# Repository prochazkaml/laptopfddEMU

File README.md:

# laptopfddEMU
AVR based laptop floppy drive emulator

Consists of 2 MCUs:
- ATmega328PB - runs the actual floppy drive emulator
- ATmega16A - serves as a serial terminal, interfaces to 3x 7-segment displays and 5 buttons

The PCB design with the ATmega328PB (TQFP32) is available in the [kicad](/kicad) directory
(note: the design is bad, the electrolytic cap needs to be as close to the MCU as possible, the current placement causes unexpected issues where the MCU resets randomly - 
just solder another cap directly to the MCU's legs from the programmer/serial side, as you've got nice big pads there).

The "PCB design" with the ATmega16A (DIP40) was improvised and cut out on a piece of raw copper PCB with a knife. No designs available for that, I'm afraid.

Apologies for the lack of documentation on this project, but I was improvising almost everything (as I needed to get this project done extra quick)
and did not keep track of progress very well. Consider building this only if you feel brave enough for it.

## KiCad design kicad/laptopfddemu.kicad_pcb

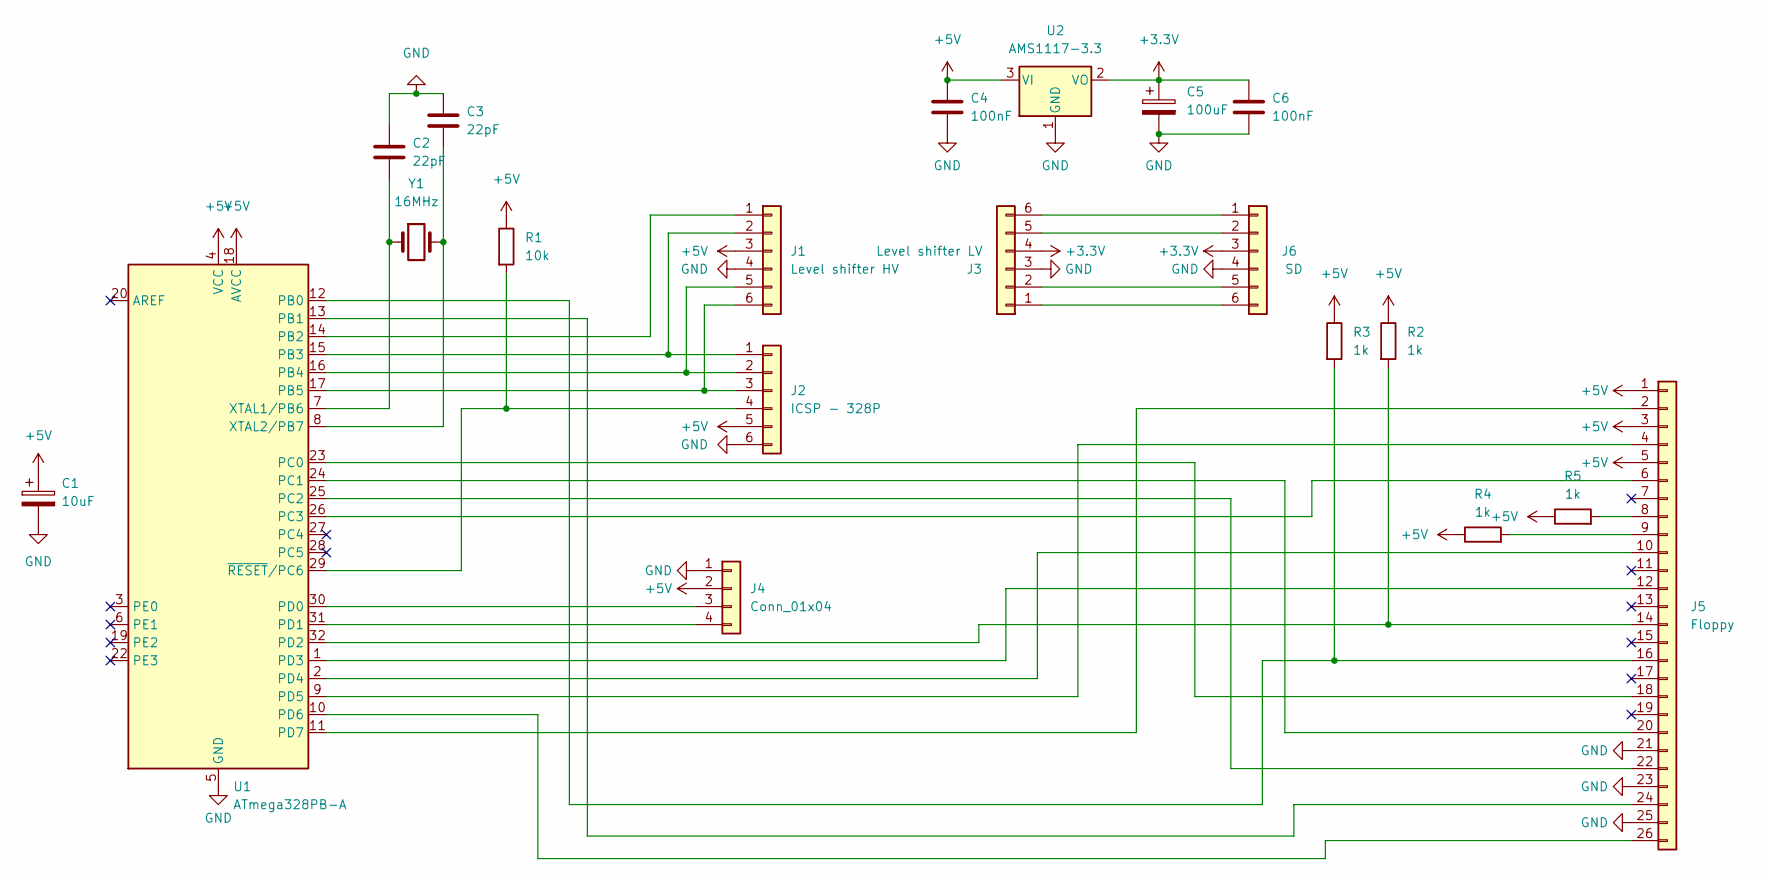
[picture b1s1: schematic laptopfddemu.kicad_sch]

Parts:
C1: 10uF; CP_Radial_D5.0mm_P2.50mm
C2, C3: 22pF; C_Disc_D7.0mm_W2.5mm_P5.00mm
C4, C6: 100nF; C_Disc_D7.0mm_W2.5mm_P5.00mm
C5: 100uF; CP_Radial_D5.0mm_P2.50mm
J1: Level shifter HV; PinHeader_1x06_P2.54mm_Vertical
J2: ICSP - 328P; PinHeader_1x06_P2.54mm_Vertical
J3: Level shifter LV; PinHeader_1x06_P2.54mm_Vertical
J4: Conn_01x04; PinHeader_1x04_P2.54mm_Vertical
J5: Floppy; TE_2-84953-6_1x26-1MP_P1.0mm_Horizontal
J6: SD; PinHeader_1x06_P2.54mm_Vertical
R1: 10k; R_Axial_DIN0207_L6.3mm_D2.5mm_P10.16mm_Horizontal
R2, R3, R4, R5: 1k; R_Axial_DIN0207_L6.3mm_D2.5mm_P10.16mm_Horizontal
U1: ATmega328PB-A; TQFP-32_7x7mm_P0.8mm
U2: AMS1117-3.3; SOT-223-3_TabPin2
Y1: 16MHz; Crystal_HC49-U_Vertical

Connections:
+3.3V: C5.1, C6.1, J3.4, J6.3, U2.2 (VO)
+5V: C1.1, C4.1, J1.3, J2.5, J4.2, J5.1, J5.3, J5.5, R1.1, R2.1, R3.1, R4.1, R5.1, U1.4 (VCC), U1.18 (AVCC), U2.3 (VI)
GND: C1.2, C2.1, C3.1, C4.2, C5.2, C6.2, J1.4, J2.6, J3.3, J4.1, J5.21, J5.23, J5.25, J5.MP, J6.4, U1.5 (GND), U1.21 (GND), U2.1 (GND)
unnamed: C2.2, U1.7 (XTAL1/PB6), Y1.1
unnamed: C3.2, U1.8 (XTAL2/PB7), Y1.2
unnamed: J1.1, U1.14 (PB2)
unnamed: J1.2, J2.1, U1.15 (PB3)
unnamed: J1.5, J2.2, U1.16 (PB4)
unnamed: J1.6, J2.3, U1.17 (PB5)
unnamed: J2.4, R1.2, U1.29 (~RESET/PC6)
unnamed: J3.1, J6.6
unnamed: J3.2, J6.5
unnamed: J3.5, J6.2
unnamed: J3.6, J6.1
unnamed: J4.3, U1.30 (PD0)
unnamed: J4.4, U1.31 (PD1)
unnamed: J5.2, U1.11 (PD7)
unnamed: J5.4, U1.9 (PD5)
unnamed: J5.6, U1.26 (PC3)
unnamed: J5.8, R5.2
unnamed: J5.9, R4.2
unnamed: J5.10, U1.2 (PD4)
unnamed: J5.12, U1.1 (PD3)
unnamed: J5.14, R2.2, U1.32 (PD2)
unnamed: J5.16, R3.2, U1.12 (PB0)
unnamed: J5.18, U1.23 (PC0)
unnamed: J5.20, U1.24 (PC1)
unnamed: J5.22, U1.25 (PC2)
unnamed: J5.24, U1.13 (PB1)
unnamed: J5.26, U1.10 (PD6)

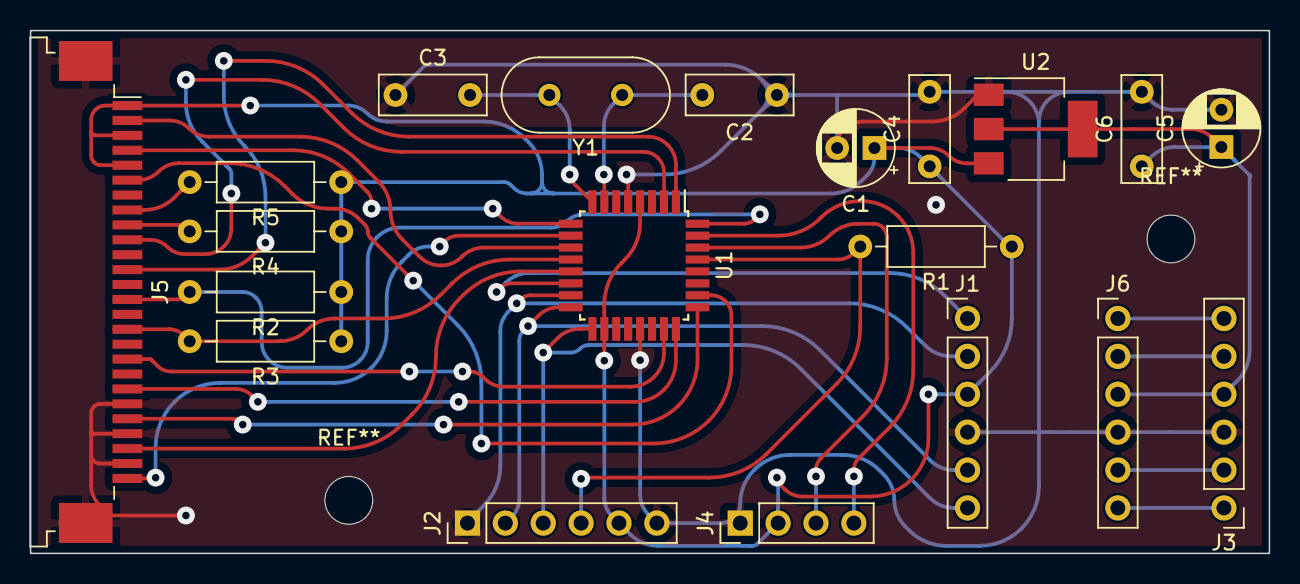
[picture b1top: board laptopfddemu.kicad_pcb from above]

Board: 2 copper layers, 83.1 x 35.1 mm, 20 parts (0 on the bottom side), 30 nets.

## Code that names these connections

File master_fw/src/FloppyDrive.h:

// -----------------------------------------------------------------------------
// This file is part of fddEMU "Floppy Disk Drive Emulator"
// Copyright (C) 2021 Acemi Elektronikci
//
// This program is free software; you can redistribute it and/or modify
// it under the terms of the GNU General Public License as published by
// the Free Software Foundation; either version 3 of the License, or
// (at your option) any later version.
//
// This program is distributed in the hope that it will be useful,
// but WITHOUT ANY WARRANTY; without even the implied warranty of
// MERCHANTABILITY or FITNESS FOR A PARTICULAR PURPOSE.  See the
// GNU General Public License for more details.
//
// You should have received a copy of the GNU General Public License
// along with this program; if not, write to the Free Software Foundation,
// Inc., 51 Franklin Street, Fifth Floor, Boston, MA 02110-1301  USA
// -----------------------------------------------------------------------------

#ifndef FLOPPYDRIVE_H
#define FLOPPYDRIVE_H

#include "FloppyDisk.h"
#include <stdint.h>

#if defined (__AVR_ATmega328P__) || defined (__AVR_ATmega328PB__)
// -------------------------------  Pin assignments for Arduino UNO/Nano/Pro Mini (Atmega328p)  ------------------------------
//PORTD
#define PIN_STEP      2
#define REG_STEP			PIND
#define PIN_STEPDIR   3
#define REG_STEPDIR		PIND
#define PIN_MOTORA    4
#define REG_MOTORA		PIND
#define PIN_SELECTA   5
#define REG_SELECTA		PIND
#define PIN_SIDE      6
#define REG_SIDE			PIND
#define PIN_INDEX     7
#define DDR_INDEX			DDRD

//PORTB
#define PIN_READDATA  0
#define DDR_READDATA	DDRB
#define PIN_WRITEDATA 1
#define DDR_WRITEDATA DDRB
//rest of PORTB pins are SPI

//PORTC
#define PIN_WRITEGATE 0
#define REG_WRITEGATE PINC
#define PIN_TRACK0    1
#define DDR_TRACK0 		DDRC
#define PIN_WRITEPROT 2
#define DDR_WRITEPROT DDRC
#define PIN_DSKCHANGE 3
#define DDR_DSKCHANGE DDRC


// -------------------------------  Pin assignments for Arduino UNO/Nano/Pro Mini (Atmega328p)  ------------------------------
#elif defined (__AVR_ATmega32U4__)
// -------------------------------  Pin assignments for Arduino (Atmega32U4)  ------------------------------
//PORTD PD0(SCL) and PD1(SDA) I2C pins (D2 and D3 on pro micro)
//PORTB PB0(SS), PB1(SCK), PB2(MISO), PB3(MOSI) SPI pins (D17, D15, D14, D16)  D17->TX led

//Unchangeable pins ICP&OCP for timer1
#define PIN_READDATA    4   //PD4 must be pin4 (ICP for timer1)
#define DDR_READDATA		DDRD
#define PIN_WRITEDATA   5   //PB5 must be pin9 (OCP for timer1)
#define DDR_WRITEDATA		DDRB
//Pin Change Interrupt pins
#define PIN_MOTORA      4   //PB4-PCINT4-pin8
#define REG_MOTORA			PINB
#define PIN_SELECTA     6   //PB6-PCINT6-pin10
#define REG_SELECTA			PINB
//External Interrupt pins
#define PIN_STEP        2   //PD2-INT2-RX1 will use external interrupt 2
#define REG_STEP				PIND
//Changeable pins
#define PIN_STEPDIR     3   //PD3-INT3-TX1
#define REG_STEPDIR			PIND
#define PIN_SIDE        6   //PC6-pin5
#define REG_SIDE				PINC
#define PIN_INDEX       7   //PD7-pin6
#define DDR_INDEX				DDRD
#define PIN_WRITEGATE   6   //PE6-INT6-pin7
#define REG_WRITEGATE		PINE
#define PIN_TRACK0      4   //PF4-pinA3
#define DDR_TRACK0			DDRF
#define PIN_WRITEPROT   5   //PD5-pin24-TXLED
#define DDR_WRITEPROT		DDRD
#define PIN_DSKCHANGE   6   //PF6-pinA1
#define DDR_DSKCHANGE		DDRF
//SS pin for SD card is PF7-pinA0 for atmega32u4 (Arduino pro micro)
//SS pin is set in "pffArduino.h" to change the pin
//also changing the macros in "pffArduino.h" is required.

// -------------------------------  Pin assignments for Arduino (Atmega32U4)  ------------------------------
#endif //defined (__AVR_ATmega32U4__)

//Output commands
#define SET_INDEX_LOW()    (DDR_INDEX |= (1 << PIN_INDEX))
#define SET_INDEX_HIGH()   (DDR_INDEX &= ~(1 << PIN_INDEX))
#define SET_TRACK0_LOW()    (DDR_TRACK0 |= (1 << PIN_TRACK0))
#define SET_TRACK0_HIGH()   (DDR_TRACK0 &= ~(1 << PIN_TRACK0))
#define SET_DSKCHANGE_LOW()    (DDR_DSKCHANGE |= (1 << PIN_DSKCHANGE))
#define SET_DSKCHANGE_HIGH()   (DDR_DSKCHANGE &= ~(1 << PIN_DSKCHANGE))
#define SET_WRITEPROT_LOW()    (DDR_WRITEPROT |= (1 << PIN_WRITEPROT))
#define SET_WRITEPROT_HIGH()   (DDR_WRITEPROT &= ~(1 << PIN_WRITEPROT))

//Inputs
#define IS_WRITE()          ( !(REG_WRITEGATE & (1 << PIN_WRITEGATE)) )
#define SIDE()              (REG_SIDE & (1 << PIN_SIDE))
#define STEPDIR()           (REG_STEPDIR & (1 << PIN_STEPDIR))
#define IS_STEP()           ( !(REG_STEP & (1 << PIN_STEP)) )
#define IS_SELECTA()        ( !(REG_SELECTA & (1 << PIN_SELECTA)) )
#define IS_MOTORA()         ( !(REG_MOTORA & (1 << PIN_MOTORA)) )
//Two drive mode requires SELECT and MOTOR pins combined trough an AND gate
//if two drive mode is enabled SELECTA pin is used for combined SELECTA & MOTORA
//and MOTORA pin is used for combined SELECTB & MOTORB

struct __attribute__((__packed__)) driveControlFlags
{
	uint8_t driveSel : 2;		
	uint8_t trackChanged : 1;
	uint8_t empty : 5;
};

class driveStatus
{
	private:
		volatile struct driveControlFlags f;		
	public:
		driveStatus() {f.driveSel = 0; f.trackChanged = 0;}
		void setTrackChanged() {f.trackChanged = 1;}
		void clrTrackChanged() {f.trackChanged = 0;}
		uint8_t isTrackChanged() {return f.trackChanged;}	
	#if ENABLE_DRIVE_B // Dual drive mode		
		uint8_t isDrive0() {return IS_SELECTA() ? (1 << 0):0;}
		uint8_t isDrive1() {return IS_MOTORA() ? (1 << 1):0;}
	#else // Single drive mode
		uint8_t isDrive0() {return IS_SELECTA() && IS_MOTORA() ? (1 << 0):0;}
		uint8_t isDrive1() {return 0;}			
	#endif // ENABLE_DRIVE_B 		
		uint8_t getDriveSel () {return isDrive1()|isDrive0();}		
		bool isDrvChanged() 
		{
			if (f.driveSel == getDriveSel()) return false;
			else f.driveSel = getDriveSel(); 
			return true;
		}		
};

struct __attribute__((__packed__)) floppySectorHeader
{
	union 
	{
		uint8_t buffer[8];
		struct __attribute__((__packed__)) 
		{
			uint8_t	id;	// sector header id: 0xFE
			uint8_t track; // current cylinder
			uint8_t	side; // current head
			uint8_t	sector;	// current sector: starts at 1
			uint8_t	length; // 0: 128b, 1: 256b, 2: 512b, 3: 1024b
			uint8_t crcHI; // crc / 256
			uint8_t	crcLO; // crc & 255
			uint8_t gap; // first byte of post-header gap: 0x4E

		};
	};
	
};

struct __attribute__((__packed__)) floppySectorData
{
	union 
	{
		uint8_t buffer[1+512+3+3];
		struct __attribute__((__packed__))
		{
			uint8_t	id; // sector data id: 0xFB
			uint8_t	data[512]; //sector data 512 bytes
			uint8_t crcHI; // crc / 256
			uint8_t	crcLO; // crc & 255
			uint8_t gap; // first byte of post-data gap: 0x4E
			uint8_t save[3]; //storage for saving half_sector data			
		};		
	};	
};

class FloppyDrive : public FloppyDisk
{
	private:
		int track;
		int getSectorData(int lba);
		int setSectorData(int lba);

	public:
		FloppyDrive();
		char *diskInfoStr();
		bool load(char *);
		void eject();
		void run();
};

#if ENABLE_DRIVE_B
		#define N_DRIVE 2
#else
		#define N_DRIVE 1
#endif //ENABLE_DRIVE_B

extern volatile uint8_t iFlags; //flags set by interrupt
extern class FloppyDrive drive[N_DRIVE];
extern class driveStatus ds;

#endif //PLOPPYDRIVE_H

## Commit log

2023-01-30 Cleanup
2023-01-30 Create LICENSE
2023-01-30 Added KiCad designs
